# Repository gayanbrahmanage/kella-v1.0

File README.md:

# kella-v1.0
 Humonoid Robot Development Project

 ### Base Design and Development
 <div style="display: flex;">

 </div>
 
 ### YouTube Video-Base Manual Mode Testing

[Watch on YouTube](https://www.youtube.com/watch?v=laG0K3bYE8s)

# Design Power Point 

[View Design PPT](photos/pdf.pdf)

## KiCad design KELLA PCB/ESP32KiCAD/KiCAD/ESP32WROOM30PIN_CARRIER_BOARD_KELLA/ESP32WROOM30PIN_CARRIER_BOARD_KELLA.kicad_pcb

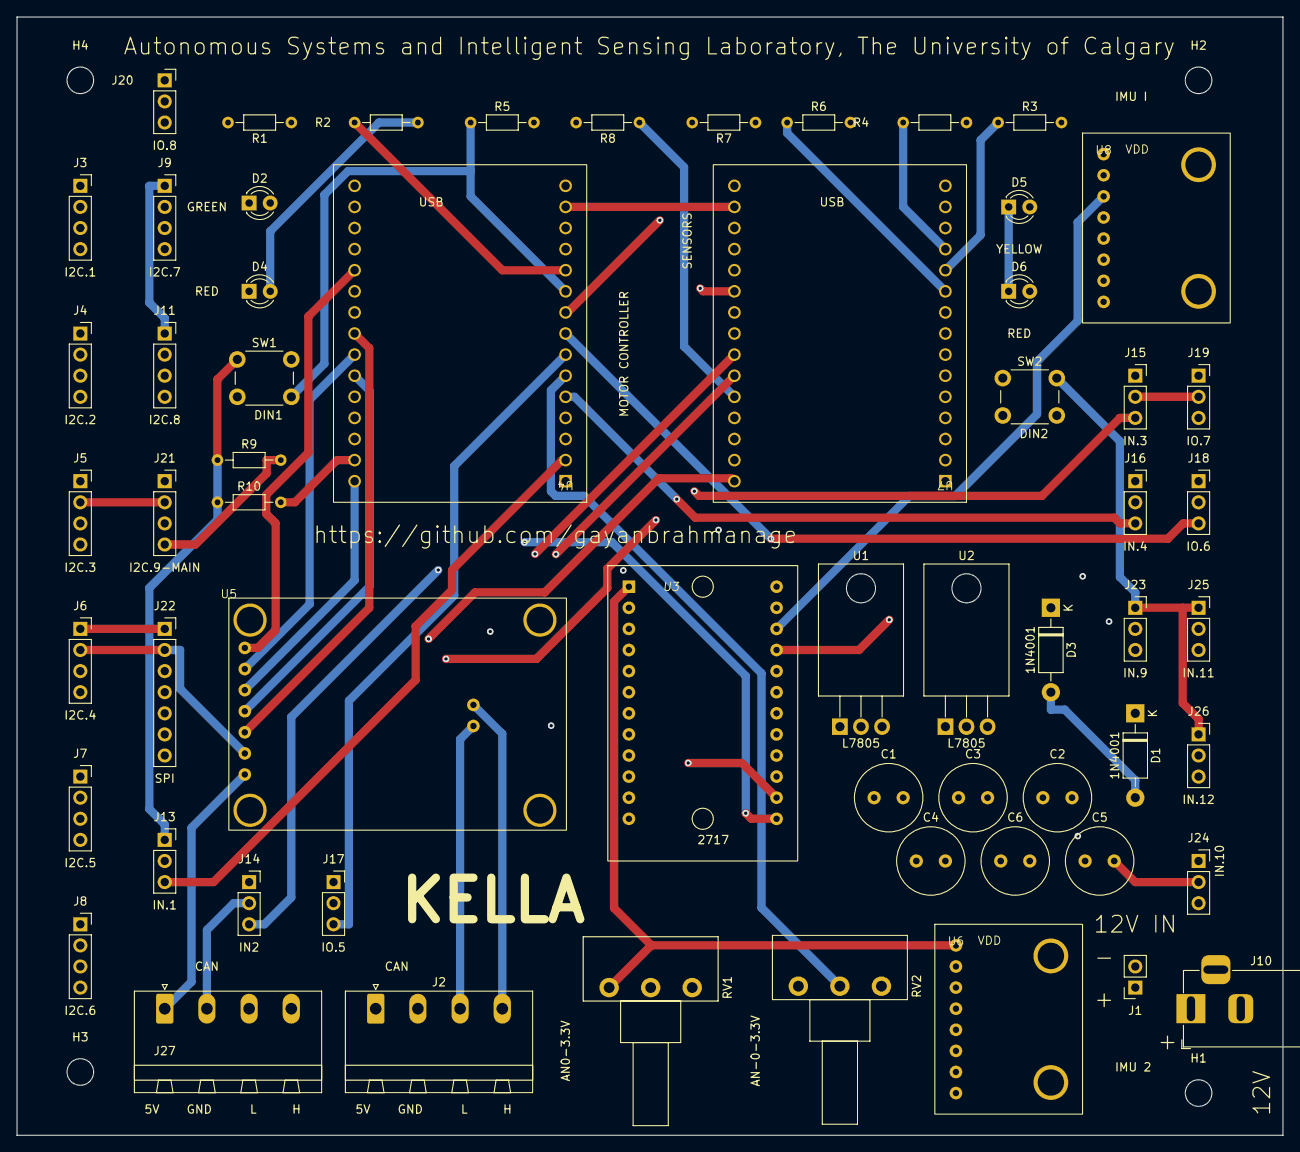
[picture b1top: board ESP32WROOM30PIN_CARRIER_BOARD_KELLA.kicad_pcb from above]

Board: 4 copper layers, 152.4 x 134.6 mm, 64 parts (0 on the bottom side), 70 nets.

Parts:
C1, C2, C3, C4, C5, C6: C; C_Radial_D8.0mm_H7.0mm_P3.50mm
D1, D3: 1N4001; D_DO-41_SOD81_P10.16mm_Horizontal
D2: GREEN; LED_D3.0mm_IRGrey
D4, D6: RED; LED_D3.0mm_IRGrey
D5: YELLOW; LED_D3.0mm_IRGrey
H1, H2, H3, H4: M; MountingHole_3.2mm_M3
J1: 12V IN; PinSocket_1x02_P2.54mm_Vertical
J2, J27: CAN; PhoenixContact_MSTBA_2,5_4-G-5,08_1x04_P5.08mm_Horizontal
J3: I2C.1; PinSocket_1x04_P2.54mm_Vertical
J4: I2C.2; PinSocket_1x04_P2.54mm_Vertical
J5: I2C.3; PinSocket_1x04_P2.54mm_Vertical
J6: I2C.4; PinSocket_1x04_P2.54mm_Vertical
J7: I2C.5; PinSocket_1x04_P2.54mm_Vertical
J8: I2C.6; PinSocket_1x04_P2.54mm_Vertical
J9: I2C.7; PinSocket_1x04_P2.54mm_Vertical
J10: 12V; BarrelJack_Horizontal
J11: I2C.8; PinSocket_1x04_P2.54mm_Vertical
J13: IN.1; PinSocket_1x03_P2.54mm_Vertical
J14: IN2; PinSocket_1x03_P2.54mm_Vertical
J15: IN.3; PinSocket_1x03_P2.54mm_Vertical
J16: IN.4; PinSocket_1x03_P2.54mm_Vertical
J17: IO.5; PinSocket_1x03_P2.54mm_Vertical
J18: IO.6; PinSocket_1x03_P2.54mm_Vertical
J19: IO.7; PinSocket_1x03_P2.54mm_Vertical
J20: IO.8; PinSocket_1x03_P2.54mm_Vertical
J21: I2C.9-MAIN; PinSocket_1x04_P2.54mm_Vertical
J22: SPI; PinSocket_1x07_P2.54mm_Vertical
J23: IN.9; PinSocket_1x03_P2.54mm_Vertical
J24: IN.10; PinSocket_1x03_P2.54mm_Vertical
J25: IN.11; PinSocket_1x03_P2.54mm_Vertical
J26: IN.12; PinSocket_1x03_P2.54mm_Vertical
R1, R2, R3, R4, R5, R6, R7, R8, R9, R10: R; R_Axial_DIN0204_L3.6mm_D1.6mm_P7.62mm_Horizontal
RV1: AN0-3.3V; Potentiometer_Piher_T-16H_Single_Horizontal
RV2: AN-0-3.3V; Potentiometer_Piher_T-16H_Single_Horizontal
SW1: DIN1; SW_PUSH_6mm_H4.3mm
SW2: DIN2; SW_PUSH_6mm_H4.3mm
U1, U2: L7805; TO-220-3_Horizontal_TabDown
U3: 2717; Module2717_TCA9548A
U4, U7: ESP32WROOM30PIN
U5: MCP2515Mf
U6, U8: MPU6050M

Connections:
GND: C1.2, C2.2, C3.2, C4.2, C5.2, C6.2, D2.1 (K), D4.1 (K), D5.1 (K), D6.1 (K), J1.2, J2.2, J3.2, J4.2, J5.2, J6.2, J7.2, J8.2, J9.2, J10.2, J11.2, J13.2, J14.2, J15.2, J16.2, J17.2, J18.2, J19.2, J20.2, J21.2, J22.2, J23.2, J24.2, J25.2, J26.2, J27.2, R5.2, R6.2, RV1.3, RV2.3, U1.2 (GND), U2.2 (GND), U3.2 (GND), U4.14 (GND), U4.17 (GND), U5.6 (GND), U6.2 (GND), U7.14 (GND), U7.17 (GND), U8.2 (GND)
unnamed: D1.2 (A), D3.2 (A), J1.1, J10.1
unnamed: D1.1 (K), U1.1 (IN)
unnamed: D2.2 (A), R1.2
unnamed: D3.1 (K), U2.1 (IN)
unnamed: D4.2 (A), R2.2
unnamed: D5.2 (A), R3.2
unnamed: D6.2 (A), R4.2
unnamed: J2.3, J27.3, U5.9 (L)
unnamed: J2.4, J27.4, U5.8 (H)
unnamed: J3.3, U3.10 (SCL0)
unnamed: J3.4, U3.9 (SDA0)
unnamed: J4.3, U3.12 (SCL1)
unnamed: J4.4, U3.11 (SDA1)
unnamed: J5.3, U3.14 (SCL2)
unnamed: J5.4, U3.13 (SDA2)
unnamed: J6.3, U3.16 (SCL3)
unnamed: J6.4, U3.15 (SDA3)
unnamed: J7.3, U3.18 (SCL4)
unnamed: J7.4, U3.17 (SDA4)
unnamed: J8.3, U3.20 (SCL5)
unnamed: J8.4, U3.19 (SDA5)
unnamed: J9.3, U3.24 (SCL7), U6.3 (SCL)
unnamed: J9.4, U3.23 (SDA7), U6.4 (SDA)
unnamed: J3.1, J4.1, J5.1, J6.1, J7.1, J8.1, J9.1, J11.1, J22.1, J23.1, J24.1, J25.1, J26.1, R7.2, R8.2, RV1.1, SW2.1 (C), U3.1 (VIN), U6.1 (VDD), U7.16 (3.3V), U8.1 (VDD)
unnamed: J11.3, U3.22 (SCL6), U8.3 (SCL)
unnamed: J11.4, U3.21 (SDA6), U8.4 (SDA)
unnamed: J13.1, J14.1, J15.1, J16.1, J17.1, J18.1, J19.1, J20.1, J21.1, R9.1, R10.1, RV2.1, SW1.1 (C), U4.16 (3.3V)
unnamed: J13.3, U4.2 (GPIO36(ADC1-CH0))
unnamed: J14.3, U4.3 (GPIO39(ADC1-CH3))
unnamed: J15.3, U4.4 (GPIO34(ADC1-CH6))
unnamed: J16.3, U4.5 (GPIO35(ADC1-CH7))
unnamed: J17.3, U4.7 (GPIO33(ADC1-CH5))
unnamed: J18.3, U4.8 (GPIO25(ADC2-CH8))
unnamed: J19.3, U4.9 (GPIO26(ADC2-CH9))
unnamed: J20.3, U4.13 (GPIO13(ADC2-CH4))
unnamed: J21.3, R10.2, U4.29 (GPIO22(SCL))
unnamed: J21.4, R9.2, U4.26 (GPIO21(SDA))
unnamed: J22.3, U7.24 (GPIO18(SCK))
unnamed: J22.4, U7.30 (GPIO23(MOSI))
unnamed: J22.5, U7.25 (GPIO19(MISO))
unnamed: J22.6, U7.23 (GPIO05(SS))
unnamed: J22.7, U7.9 (GPIO26(ADC2-CH9))
unnamed: J23.3, U7.2 (GPIO36(ADC1-CH0))
unnamed: J24.3, U7.3 (GPIO39(ADC1-CH3))
unnamed: J25.3, U7.4 (GPIO34(ADC1-CH6))
unnamed: J26.3, U7.5 (GPIO35(ADC1-CH7))
unnamed: R5.1, SW1.2 (D), U4.10 (GPIO27(ADC2-CH7))
unnamed: R6.1, SW2.2 (D), U7.10 (GPIO27(ADC2-CH7))
unnamed: U3.6 (A0), U7.20 (GPIO04(ADC2-CH0))
unnamed: U3.7 (A1), U7.8 (GPIO25(ADC2-CH8))
unnamed: U3.8 (A2), U7.7 (GPIO33(ADC1-CH5))
unnamed: U3.5 (RST), U7.13 (GPIO13(ADC2-CH4))
unnamed: R7.1, U3.4 (SCL), U7.29 (GPIO22(SCL))
unnamed: R8.1, U3.3 (SDA), U7.26 (GPIO21(SDA))
unnamed: U4.20 (GPIO04(ADC2-CH0)), U5.1 (INT)
unnamed: U4.23 (GPIO05(SS)), U5.5 (CS)
unnamed: R1.1, U4.12 (GPIO12(ADC2-CH5))
unnamed: R2.1, U4.11 (GPIO14(ADC2-CH6))
unnamed: U4.21 (GPIO16(RXD2)), U7.22 (GPIO17(TXD2))
unnamed: U4.22 (GPIO17(TXD2)), U7.21 (GPIO16(RXD2))
unnamed: U4.24 (GPIO18(SCK)), U5.2 (SCK)
unnamed: U4.25 (GPIO19(MISO)), U5.4 (SO)
unnamed: U4.30 (GPIO23(MOSI)), U5.3 (SI)
unnamed: RV2.2, U4.6 (GPIO32(ADC1-CH4))
unnamed: R4.1, U7.12 (GPIO12(ADC2-CH5))
unnamed: R3.1, U7.11 (GPIO14(ADC2-CH6))
unnamed: RV1.2, U7.6 (GPIO32(ADC1-CH4))
VDD1: C1.1, C2.1, C3.1, U1.3 (OUT), U7.15 (VDD)
VDD2: C4.1, C5.1, C6.1, J2.1, J27.1, U2.3 (OUT), U4.15 (VDD), U5.7 (VCC)

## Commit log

2024-05-02 Added pcb files
2024-08-21 Changed pcb to KiCAD
2024-08-21 updated PCB
2024-08-21 Picture esp32 added
2024-08-22 Added soldered
2024-08-22 Added printed PCB
2024-08-29 Added photos
2024-08-29 Photo Added
2024-08-30 Added PPT
2024-09-04 Esp32code updated
2024-09-06 added x4-3
2024-09-08 Myactuator test added
2024-09-28 CPP CAN added
2024-10-03 CPP updated
